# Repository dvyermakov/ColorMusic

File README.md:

### Название

Цветомузыка

### Цели

- Воплотить давнюю задумку.
- Получить опыт разработки аналоговых устройств (усилитель и расчет фильтров).

### Описание

Устройство служит для светового сопровождения музыкальных произведений. 
Состоит из четырех ламп (синего, зеленого, желтого и красного цветов) и блока управления.
Блок питания можно взять любой с напряжением 12 В и силой тока удовлетворяющей нагрузке.

Диапазон звуковой частоты разделен на четыре интервала:
- до 300 Гц для красной лампы
- 300 - 3000 Гц для желтой лампы
- 3000 - 6000 Гц для зеленой лампы
- от 6000 Гц для синей лампы

Лампы выполнены в виде соединенных последовательно-параллельно светодиодов.

В блоке управления все узлы выполнены на отдельных платах для возможности модификации и внесения изменений.

##### Список узлов (плат):
- регуляторы (переменные резисторы)
- усилитель (на ОУ LM358)
- фильтры (полосовые Баттерворта 1 порядка на ОУ LM358)
- ключи (выполнены на полевых транзисторах)
- плата разводки питания

### Использованное ПО, библиотеки.

Разработка схемы и плат - KiCad 7.0.1

### Внешний вид

### Структурная схема

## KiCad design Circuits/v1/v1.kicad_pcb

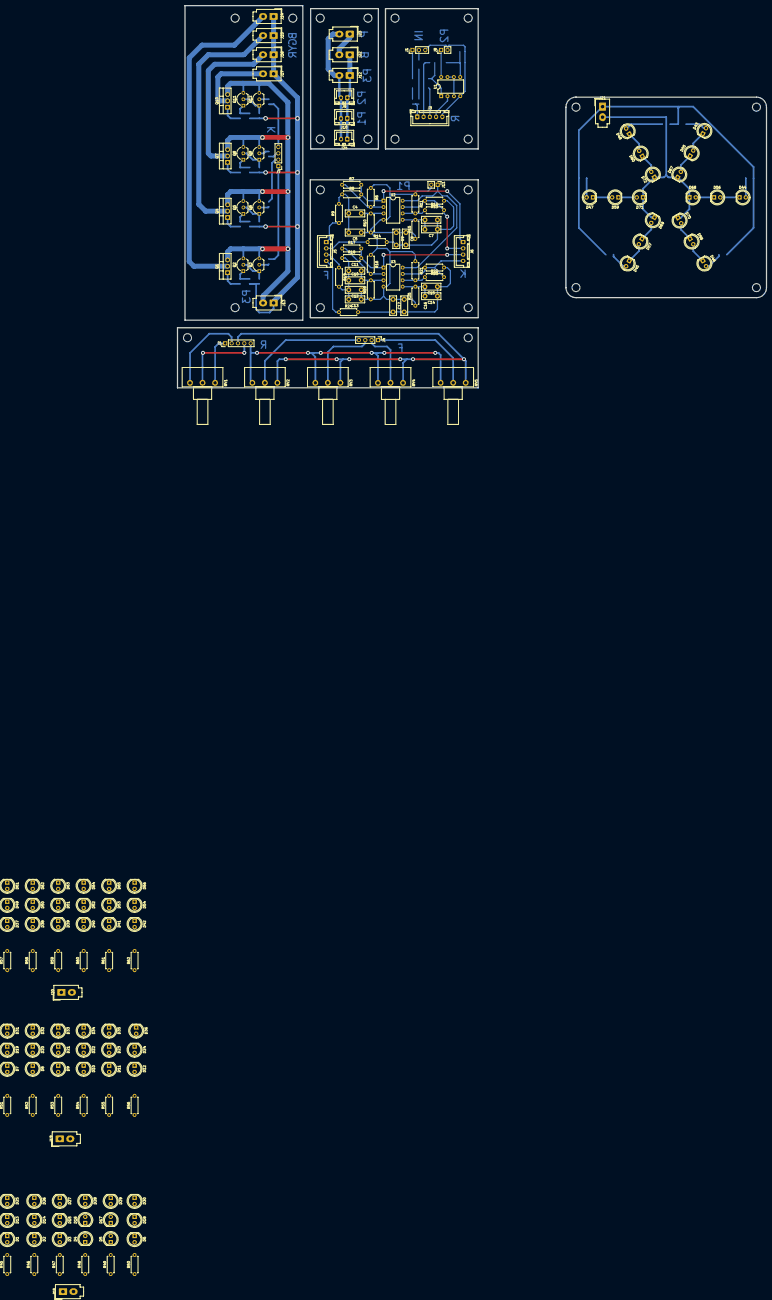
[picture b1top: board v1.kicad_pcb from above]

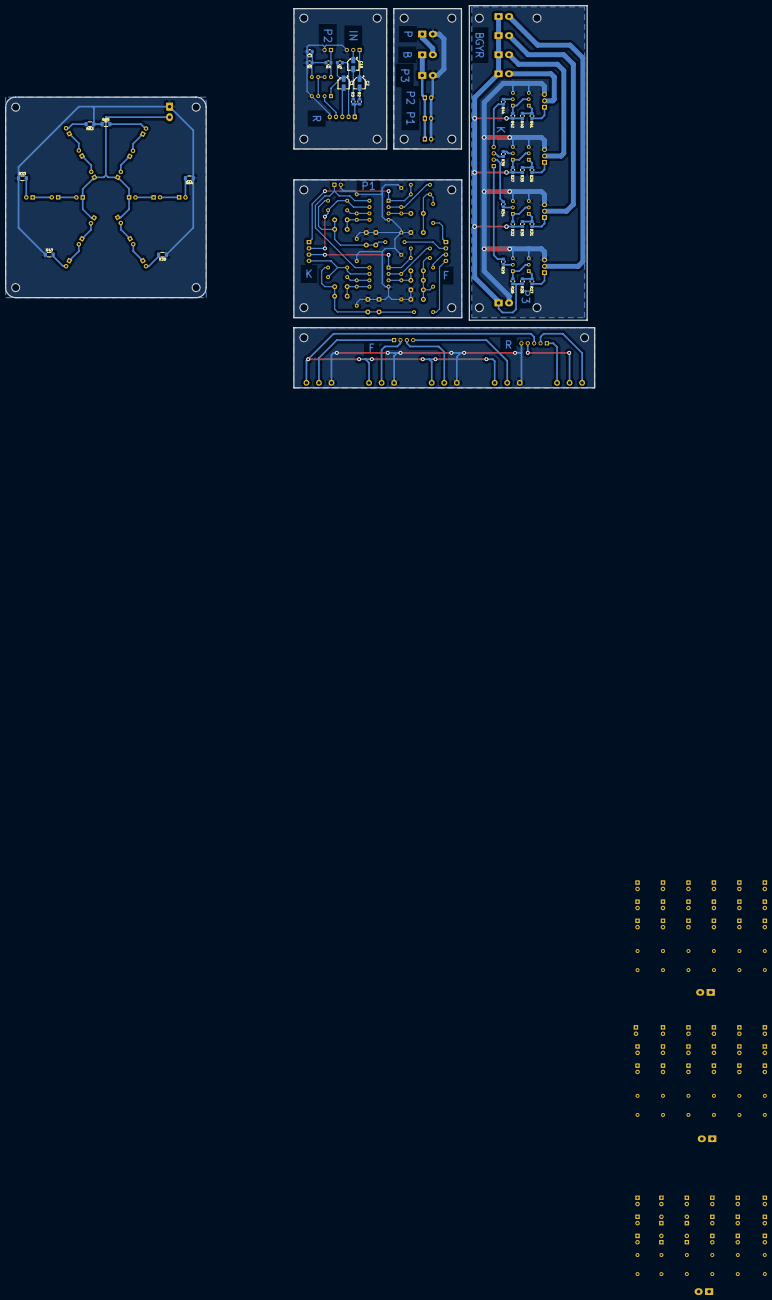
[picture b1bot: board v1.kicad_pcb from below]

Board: 2 copper layers, 235.0 x 152.5 mm, 221 parts (31 on the bottom side), 153 nets.

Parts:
C1, C2, C18: 1 u; CP_Elec_4x3
C3: 100 n; C_0805_2012Metric_Pad1.18x1.45mm_HandSolder
C4, C5: 3,3 n; C_Disc_D7.5mm_W2.5mm_P5.00mm
C6, C8, C10, C12, C15, C17: 10 n; C_Disc_D7.5mm_W2.5mm_P5.00mm
C7, C9, C11, C13: 1 n; C_Disc_D7.5mm_W2.5mm_P5.00mm
C14, C16: 100 n; C_Disc_D7.5mm_W2.5mm_P5.00mm
D1, D2, D3, D4, D5, D6, D7, D8, D9, D10, D11, D12, D13, D14, D15, D16, D17, D18, D19, D20, D21, D22, D23, D24, D25, D26, D27, D28, D29, D30, D31, D32, D33, D34, D35, D36, D37, D38, D39, D40, D41, D42, D43, D44, D45, D46, D47, D48, D49, D50, D51, D52, D53, D54, D55, D56, D57, D58, D59, D60, D61, D62, D63, D64, D65, D66, D67, D68, D69, D70, D71, D72: LED; LED_D5.0mm
H1, H2, H3, H4, H5, H6, H7, H8, H9, H10, H11, H12, H13, H14, H15, H16, H17, H18, H19, H20, H21, H22: MountingHole; MountingHole_3.2mm_M3
J1: LineIn; PinHeader_1x03_P2.54mm_Vertical
J2: Conn_01x05_Socket; PinHeader_1x05_P2.54mm_Vertical
J3: Conn_01x05_Pin; JST_XH_B5B-XH-A_1x05_P2.50mm_Vertical
J4, J7: Conn_01x04_Socket; PinHeader_1x04_P2.54mm_Vertical
J5, J6: Conn_01x04_Pin; JST_XH_B4B-XH-A_1x04_P2.50mm_Vertical
J8, J11: Conn_01x02_Socket; PinHeader_1x02_P2.54mm_Vertical
J9, J10, J24: Conn_01x02_Pin; JST_XH_B2B-XH-A_1x02_P2.50mm_Vertical
J12, J23: Conn_01x02_Pin; Molex_Mini-Fit_Jr_5566-02A_2x01_P4.20mm_Vertical
J13: Conn_01x02_Socket; Molex_Mini-Fit_Jr_5566-02A_2x01_P4.20mm_Vertical
J14, J18: Blue; Molex_Mini-Fit_Jr_5566-02A_2x01_P4.20mm_Vertical
J15, J19: Green; Molex_Mini-Fit_Jr_5566-02A_2x01_P4.20mm_Vertical
J16, J20: Yellow; Molex_Mini-Fit_Jr_5566-02A_2x01_P4.20mm_Vertical
J17, J21: Red; Molex_Mini-Fit_Jr_5566-02A_2x01_P4.20mm_Vertical
J22: Molex_Mini-Fit_Jr_5566-02A_2x01_P4.20mm_Vertical
Q1, Q4, Q7, Q10: IRF540N; TO-220-3_Vertical
Q2, Q3, Q5, Q6, Q8, Q9, Q11, Q12: BC547; TO-92_Inline_Wide
R1: 100 k; R_0805_2012Metric_Pad1.20x1.40mm_HandSolder
R2, R3, R26, R28, R30, R32, R35, R37, R40, R42: 10 k; R_0805_2012Metric_Pad1.20x1.40mm_HandSolder
R4: 330 k; R_0805_2012Metric_Pad1.20x1.40mm_HandSolder
R5: 150 k; R_0805_2012Metric_Pad1.20x1.40mm_HandSolder
R6, R7, R9, R11, R12, R14, R16, R17, R19, R21, R22, R24: 10 k; R_Axial_DIN0207_L6.3mm_D2.5mm_P7.62mm_Horizontal
R8: 4,7 k; R_Axial_DIN0207_L6.3mm_D2.5mm_P7.62mm_Horizontal
R10: 5,6 k; R_Axial_DIN0207_L6.3mm_D2.5mm_P7.62mm_Horizontal
R13: 2,7 k; R_Axial_DIN0207_L6.3mm_D2.5mm_P7.62mm_Horizontal
R15: 4,3 k; R_Axial_DIN0207_L6.3mm_D2.5mm_P7.62mm_Horizontal
R18: 15 k; R_Axial_DIN0207_L6.3mm_D2.5mm_P7.62mm_Horizontal
R20: 12 k; R_Axial_DIN0207_L6.3mm_D2.5mm_P7.62mm_Horizontal
R23: 24 k; R_Axial_DIN0207_L6.3mm_D2.5mm_P7.62mm_Horizontal
R25: 13 k; R_Axial_DIN0207_L6.3mm_D2.5mm_P7.62mm_Horizontal
R27, R31, R36, R41: 100; R_0805_2012Metric_Pad1.20x1.40mm_HandSolder
R29, R34, R39, R44: 1 k; R_0805_2012Metric_Pad1.20x1.40mm_HandSolder
R33, R38, R43, R63, R64, R65: 390; R_1206_3216Metric_Pad1.30x1.75mm_HandSolder
R45, R46, R47, R48, R49, R50, R51, R52, R53, R54, R55, R56: 180; R_Axial_DIN0207_L6.3mm_D2.5mm_P7.62mm_Horizontal
R57, R58, R59, R60, R61, R62: 390; R_Axial_DIN0207_L6.3mm_D2.5mm_P7.62mm_Horizontal
RV1, RV2, RV3, RV4, RV5: 10 k; Potentiometer_Piher_T-16H_Single_Horizontal
U1, U2, U3: LM358; DIP-8_W7.62mm

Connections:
/Блок питания/+12V: J9.1, J10.1, J12.1, J22.1, J24.1
/Блок питания/GND: J9.2, J10.2, J12.2, J23.2, J24.2
/Ключи/Keys12V: J13.1, J14.1, J15.1, J16.1, J17.1, R26.1, R28.1, R30.1, R32.1, R35.1, R37.1, R40.1, R42.1
/Ключи/KeysBChannel: J7.1, R29.2
/Ключи/KeysGChannel: J7.2, R34.2
/Ключи/KeysGND: J13.2, Q1.3 (S), Q2.3 (E), Q3.3 (E), Q4.3 (S), Q5.3 (E), Q6.3 (E), Q7.3 (S), Q8.3 (E), Q9.3 (E), Q10.3 (S), Q11.3 (E), Q12.3 (E)
/Ключи/KeysRChannel: J7.4, R44.2
/Ключи/KeysYChannel: J7.3, R39.2
/Ключи/LampBlue: J14.2, Q1.2 (D)
/Ключи/LampGreen: J15.2, Q4.2 (D)
/Ключи/LampRed: J17.2, Q10.2 (D)
/Ключи/LampYellow: J16.2, Q7.2 (D)
/Лампы/LampBlue12V: J18.1, R45.1, R46.1, R47.1, R48.1, R49.1, R50.1
/Лампы/LampBlueIn: D25.1 (K), D26.1 (K), D27.1 (K), D28.1 (K), D29.1 (K), D30.1 (K), J18.2
/Лампы/LampGreen12V: J19.1, R51.1, R52.1, R53.1, R54.1, R55.1, R56.1
/Лампы/LampGreenIn: D31.1 (K), D32.1 (K), D33.1 (K), D34.1 (K), D35.1 (K), D36.1 (K), J19.2
/Лампы/LampRed12V: J21.1, R33.1, R38.1, R43.1, R63.1, R64.1, R65.1
/Лампы/LampRedIn: D67.1 (K), D68.1 (K), D69.1 (K), D70.1 (K), D71.1 (K), D72.1 (K), J21.2
/Лампы/LampYellow12V: J20.1, R57.1, R58.1, R59.1, R60.1, R61.1, R62.1
/Лампы/LampYellowIn: D61.1 (K), D62.1 (K), D63.1 (K), D64.1 (K), D65.1 (K), D66.1 (K), J20.2
/Регуляторы/RegAmpOut: J2.3, RV2.3, RV3.3, RV4.3, RV5.3
/Регуляторы/RegBLevel: J4.1, RV5.2
/Регуляторы/RegComLevel1: J2.2, RV1.1
/Регуляторы/RegComLevel2: J2.4, RV1.2
/Регуляторы/RegComLevel3: J2.1, RV1.3
/Регуляторы/RegGLevel: J4.2, RV4.2
/Регуляторы/RegGND: J2.5, RV2.1, RV3.1, RV4.1, RV5.1
/Регуляторы/RegRLevel: J4.4, RV2.2
/Регуляторы/RegYLevel: J4.3, RV3.2
/Усилитель/Amp12V: J8.1, R4.1, U1.8 (V+)
/Усилитель/AmpComLevel1: J3.2, R1.2
/Усилитель/AmpComLevel2: J3.4, U1.2 (-)
/Усилитель/AmpComLevel3: J3.1, R2.1, R3.1
/Усилитель/AmpGND: C3.2, J1.3, J3.5, J8.2, R5.2, U1.4 (V-)
/Усилитель/AmpOut: C1.2, J3.3
/Усилитель/LineInL: C18.1, J1.2
/Усилитель/LineInR: C2.1, J1.1
/Фильтры/Fil12V: J11.1, U2.8 (V+), U3.8 (V+)
/Фильтры/FilBChannel: J6.1, R7.2, R8.2, U2.1
/Фильтры/FilBLevel: J5.1, R9.1
/Фильтры/FilGChannel: J6.2, R12.2, R13.2, U2.7
/Фильтры/FilGLevel: J5.2, R14.1
/Фильтры/FilGND: C5.1, C8.1, C9.1, C12.1, C13.1, C16.1, C17.1, J11.2, R6.1, R10.1, R11.1, R15.1, R16.1, R20.1, R21.1, R25.1, U2.4 (V-), U3.4 (V-)
/Фильтры/FilRChannel: J6.4, R22.2, R23.2, U3.7
/Фильтры/FilRLevel: J5.4, R24.1
/Фильтры/FilYChannel: J6.3, R17.2, R18.2, U3.1
/Фильтры/FilYLevel: J5.3, R19.1
GNDREF: U1.3 (+), U1.6 (-), U1.7
unnamed: C1.1, R1.1, U1.1
unnamed: C2.2, R2.2
unnamed: C4.1, C5.2, R8.1, R9.2
unnamed: C6.1, C7.1, C8.2, C9.2, R13.1, R14.2
unnamed: C10.1, C11.1, C12.2, C13.2, R18.1, R19.2
unnamed: C14.1, C15.1, C16.2, C17.2, R23.1, R24.2
unnamed: C18.2, R3.2
unnamed: D1.2 (A), R45.2
unnamed: D1.1 (K), D13.2 (A)
unnamed: D2.2 (A), R46.2
unnamed: D3.2 (A), R47.2
unnamed: D4.2 (A), R48.2
unnamed: D5.2 (A), R49.2
unnamed: D6.2 (A), R50.2
unnamed: D7.2 (A), R51.2
unnamed: D8.2 (A), R52.2
unnamed: D9.2 (A), R53.2
unnamed: D10.2 (A), R54.2
unnamed: D10.1 (K), D22.2 (A)
unnamed: D11.2 (A), R55.2
unnamed: D11.1 (K), D23.2 (A)
unnamed: D12.2 (A), R56.2
unnamed: D12.1 (K), D24.2 (A)
unnamed: D13.1 (K), D25.2 (A)
unnamed: D2.1 (K), D14.2 (A)
unnamed: D14.1 (K), D26.2 (A)
unnamed: D3.1 (K), D15.2 (A)
unnamed: D15.1 (K), D27.2 (A)
unnamed: D4.1 (K), D16.2 (A)
unnamed: D16.1 (K), D28.2 (A)
unnamed: D5.1 (K), D17.2 (A)
unnamed: D17.1 (K), D29.2 (A)
unnamed: D6.1 (K), D18.2 (A)
unnamed: D18.1 (K), D30.2 (A)
unnamed: D7.1 (K), D19.2 (A)
unnamed: D19.1 (K), D31.2 (A)
unnamed: D8.1 (K), D20.2 (A)
unnamed: D20.1 (K), D32.2 (A)
unnamed: D9.1 (K), D21.2 (A)
unnamed: D21.1 (K), D33.2 (A)
unnamed: D22.1 (K), D34.2 (A)
unnamed: D23.1 (K), D35.2 (A)
unnamed: D24.1 (K), D36.2 (A)
unnamed: D37.2 (A), R57.2
unnamed: D37.1 (K), D49.2 (A)
unnamed: D38.2 (A), R58.2
unnamed: D38.1 (K), D50.2 (A)
unnamed: D39.2 (A), R59.2
unnamed: D39.1 (K), D51.2 (A)
unnamed: D40.2 (A), R60.2
unnamed: D40.1 (K), D52.2 (A)
unnamed: D41.2 (A), R61.2
unnamed: D41.1 (K), D53.2 (A)
unnamed: D42.2 (A), R62.2
unnamed: D42.1 (K), D54.2 (A)
unnamed: D43.2 (A), R63.2
unnamed: D43.1 (K), D55.2 (A)
unnamed: D44.2 (A), R33.2
unnamed: D44.1 (K), D56.2 (A)
unnamed: D45.2 (A), R38.2
unnamed: D45.1 (K), D57.2 (A)
unnamed: D46.2 (A), R43.2
unnamed: D46.1 (K), D58.2 (A)
unnamed: D47.2 (A), R64.2
unnamed: D47.1 (K), D59.2 (A)
unnamed: D48.2 (A), R65.2
unnamed: D48.1 (K), D60.2 (A)
unnamed: D49.1 (K), D61.2 (A)
unnamed: D50.1 (K), D62.2 (A)
unnamed: D51.1 (K), D63.2 (A)
unnamed: D52.1 (K), D64.2 (A)
unnamed: D53.1 (K), D65.2 (A)
unnamed: D54.1 (K), D66.2 (A)
unnamed: D55.1 (K), D67.2 (A)
unnamed: D56.1 (K), D68.2 (A)
unnamed: D57.1 (K), D69.2 (A)
unnamed: D58.1 (K), D70.2 (A)
unnamed: D59.1 (K), D71.2 (A)
unnamed: D60.1 (K), D72.2 (A)
unnamed: J22.2, J23.1
unnamed: Q1.1 (G), R27.1
unnamed: Q2.2 (B), Q3.1 (C), R28.2
unnamed: Q2.1 (C), R26.2, R27.2
unnamed: Q3.2 (B), R29.1
unnamed: Q4.1 (G), R31.1
unnamed: Q5.2 (B), Q6.1 (C), R32.2
unnamed: Q5.1 (C), R30.2, R31.2
unnamed: Q6.2 (B), R34.1
unnamed: Q7.1 (G), R36.1
unnamed: Q8.2 (B), Q9.1 (C), R37.2
unnamed: Q8.1 (C), R35.2, R36.2
unnamed: Q9.2 (B), R39.1
unnamed: Q10.1 (G), R41.1
unnamed: Q11.2 (B), Q12.1 (C), R42.2
unnamed: Q11.1 (C), R40.2, R41.2
unnamed: Q12.2 (B), R44.1
unnamed: C3.1, R4.2, R5.1, U1.5 (+)
unnamed: C4.2, R10.2, U2.3 (+)
unnamed: R6.2, R7.1, U2.2 (-)
unnamed: C6.2, C7.2, R15.2, U2.5 (+)
unnamed: R11.2, R12.1, U2.6 (-)
unnamed: C10.2, C11.2, R20.2, U3.3 (+)
unnamed: R16.2, R17.1, U3.2 (-)
unnamed: C14.2, C15.2, R25.2, U3.5 (+)
unnamed: R21.2, R22.1, U3.6 (-)

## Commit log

2023-12-16 Initial
